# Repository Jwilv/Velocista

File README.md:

# Velocista, repocitorio de esquematicos, pcb y codigos de robots velocistas.

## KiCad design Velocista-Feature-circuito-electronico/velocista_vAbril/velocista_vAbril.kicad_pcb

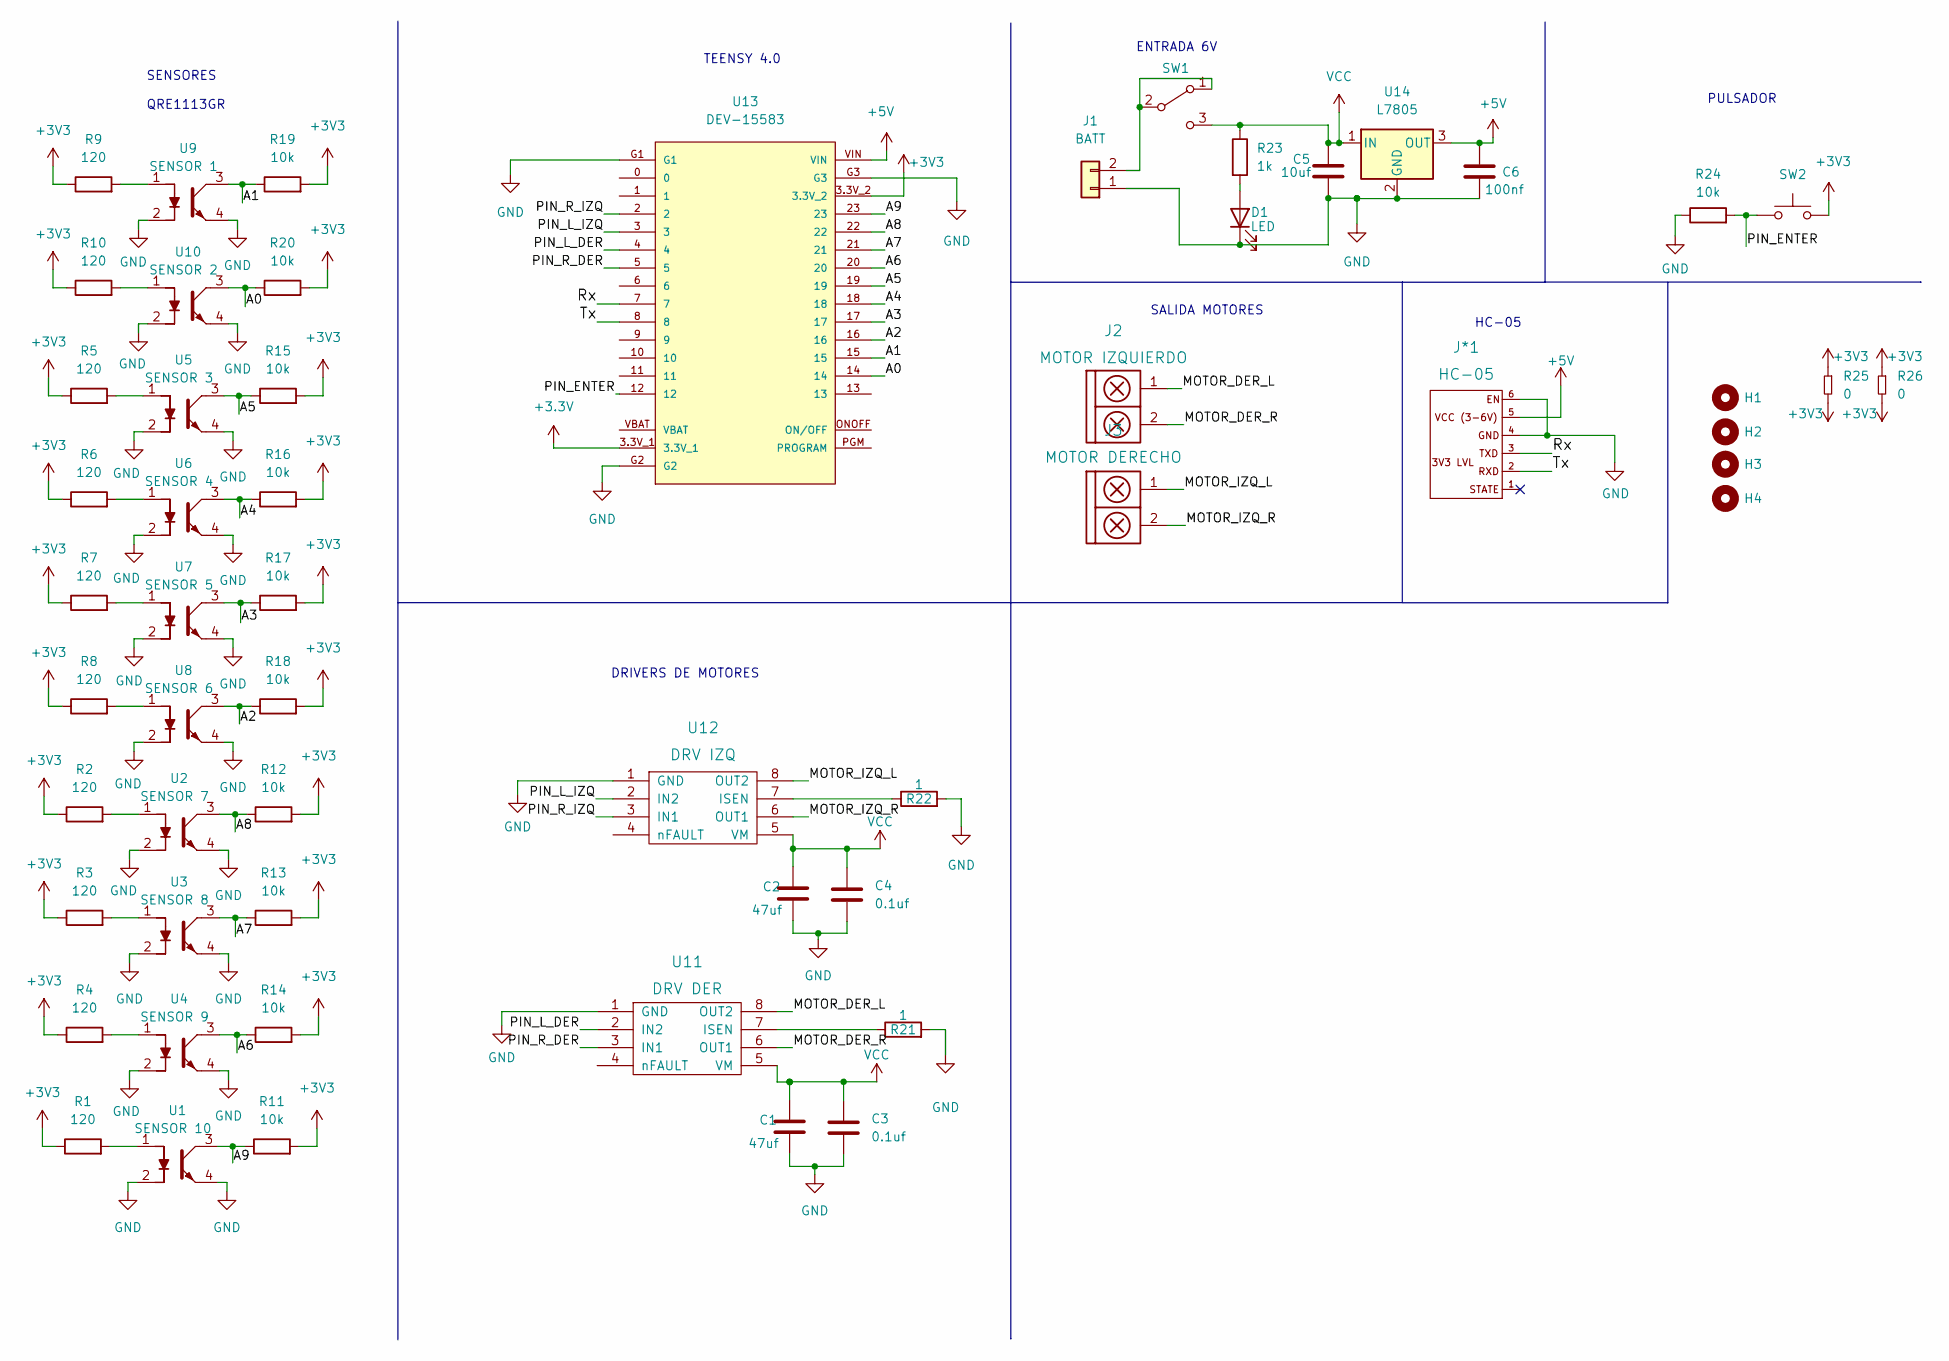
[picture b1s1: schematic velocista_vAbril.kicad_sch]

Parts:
C1, C2: 47uf; C_0805
C3, C4: 0.1uf; C_0805
C5: 10uf; C_0805
C6: 100nf; C_0805
D1: LED; led_3mm_clear
H1, H3: Mounting_Hole; hole_3mm
H2, H4: Mounting_Hole; Pololu_Micro_Con_Soporte_Simple
J1: BATT; JST_PH_B2B-PH-K_1x02_P2.00mm_Vertical
J2: MOTOR IZQUIERDO; JST_EH_B2B-EH-A_1x02_P2.50mm_Vertical
J3: MOTOR DERECHO; JST_EH_B2B-EH-A_1x02_P2.50mm_Vertical
J*1: HC-05
R1, R2, R3, R4, R5, R6, R7, R8, R9, R10: 120; R_0805
R11, R12, R13, R14, R15, R16, R17, R18, R19, R20, R24: 10k; R_0805
R21, R22: 1; R_0805
R23: 1k; R_0805
R25, R26: 0; RES0.3
SW1: SW_SPDT; SW_SPDT_TH_Vertical
SW2: SW_Push; Pulsador_TH_4
U1, U2, U3, U4, U5, U6, U7, U8, U9, U10: QRE1113; SOIC180P460X187-4N
U11: DRV DER; SSOP-8
U12: DRV IZQ; SSOP-8
U13: DEV-15583; MODULE_DEV-15583
U14: L7805; SOT223

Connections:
+5V: C6.1, J*1.5, U13.VIN, U14.3 (OUT)
/A0: R20.1, U10.3, U13.14
/A1: R19.1, U9.3, U13.15
/A2: R18.1, U8.3, U13.16
/A3: R17.1, U7.3, U13.17
/A4: R16.1, U6.3, U13.18
/A5: R15.1, U5.3, U13.19
/A6: R14.1, U4.3, U13.20
/A7: R13.1, U3.3, U13.21
/A8: R12.1, U2.3, U13.22
/A9: R11.1, U1.3, U13.23
/MOTOR_DER_L: J2.1, U11.8 (OUT2)
/MOTOR_DER_R: J2.2, U11.6 (OUT1)
/MOTOR_IZQ_L: J3.1, U12.8 (OUT2)
/MOTOR_IZQ_R: J3.2, U12.6 (OUT1)
/PIN_ENTER: R24.2, SW2.1, U13.12
/PIN_L_DER: U11.2 (IN2), U13.4
/PIN_L_IZQ: U12.2 (IN2), U13.3
/PIN_R_DER: U11.3 (IN1), U13.5
/PIN_R_IZQ: U12.3 (IN1), U13.2
/Rx: J*1.3, U13.7
/Tx: J*1.2, U13.8
GND: C1.2, C2.2, C3.2, C4.2, C5.2, C6.2, D1.1 (K), J1.1, J*1.4, J*1.6, R21.2, R22.2, R24.1, U1.2, U1.4, U2.2, U2.4, U3.2, U3.4, U4.2, U4.4, U5.2, U5.4, U6.2, U6.4, U7.2, U7.4, U8.2, U8.4, U9.2, U9.4, U10.2, U10.4, U11.1 (GND), U12.1 (GND), U13.G1, U13.G2, U13.G3, U14.2 (GND)
unnamed: D1.2 (A), R23.2
unnamed: J1.2, SW1.1 (A), SW1.2 (B)
unnamed: R1.2, U1.1
unnamed: R2.2, U2.1
unnamed: R3.2, U3.1
unnamed: R4.2, U4.1
unnamed: R5.2, U5.1
unnamed: R6.2, U6.1
unnamed: R7.2, U7.1
unnamed: R8.2, U8.1
unnamed: R9.2, U9.1
unnamed: R10.2, U10.1
unnamed: R21.1, U11.7 (ISEN)
unnamed: R22.1, U12.7 (ISEN)
VCC: C1.1, C2.1, C3.1, C4.1, C5.1, R23.1, SW1.3 (C), U11.5 (VM), U12.5 (VM), U14.1 (IN)

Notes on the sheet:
HC-05
DRIVERS DE MOTORES
ENTRADA 6V
SENSORES QRE1113GR
SALIDA MOTORES
TEENSY 4.0
PULSADOR

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
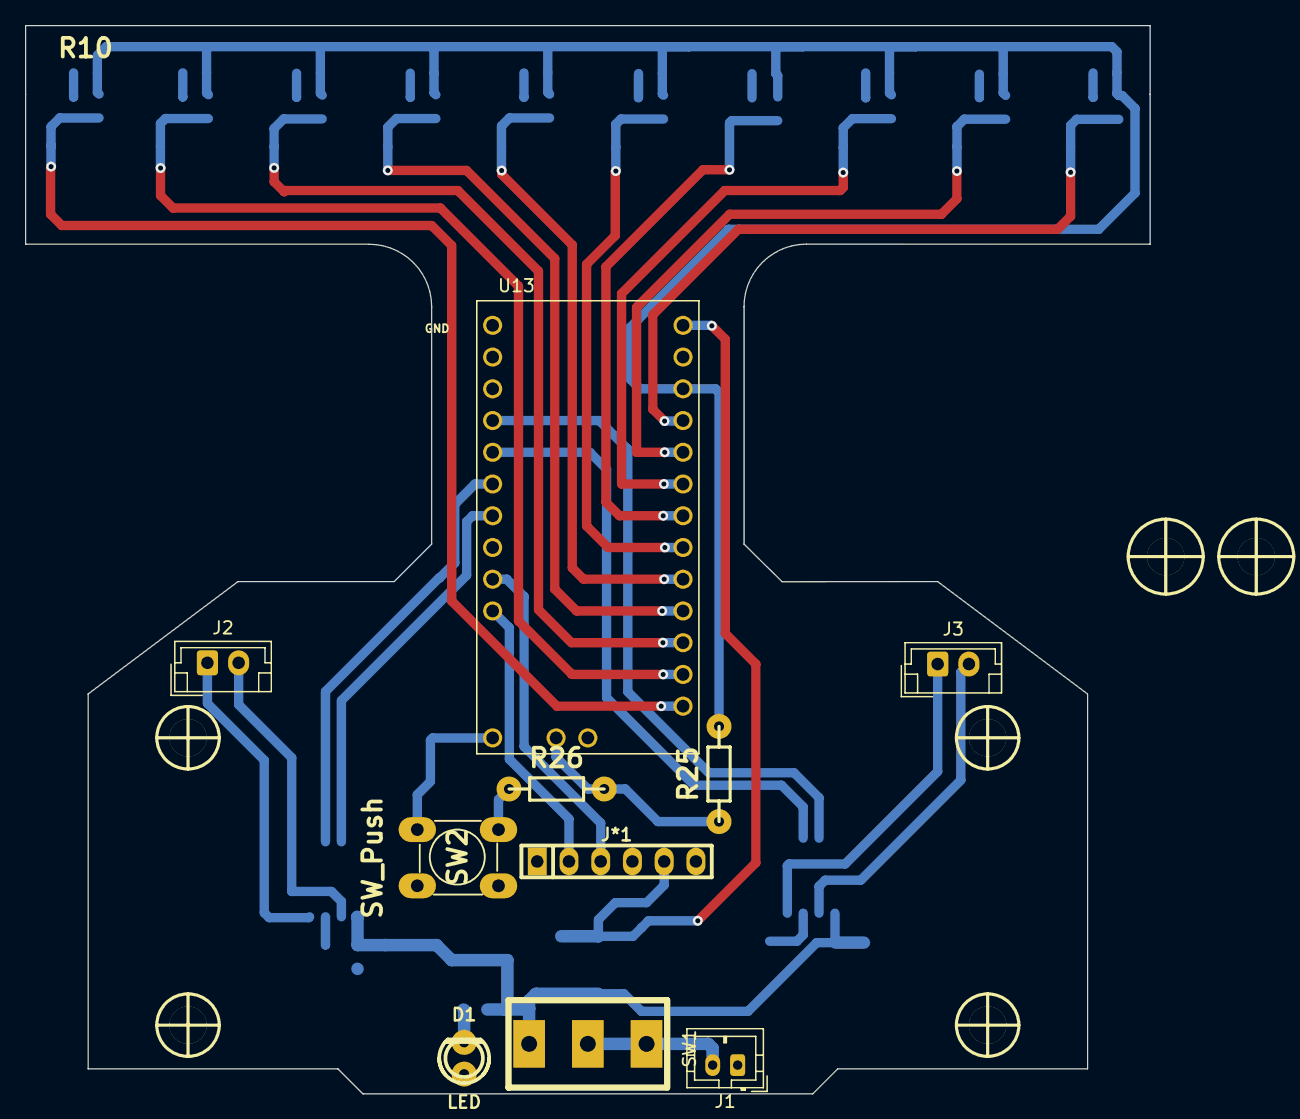
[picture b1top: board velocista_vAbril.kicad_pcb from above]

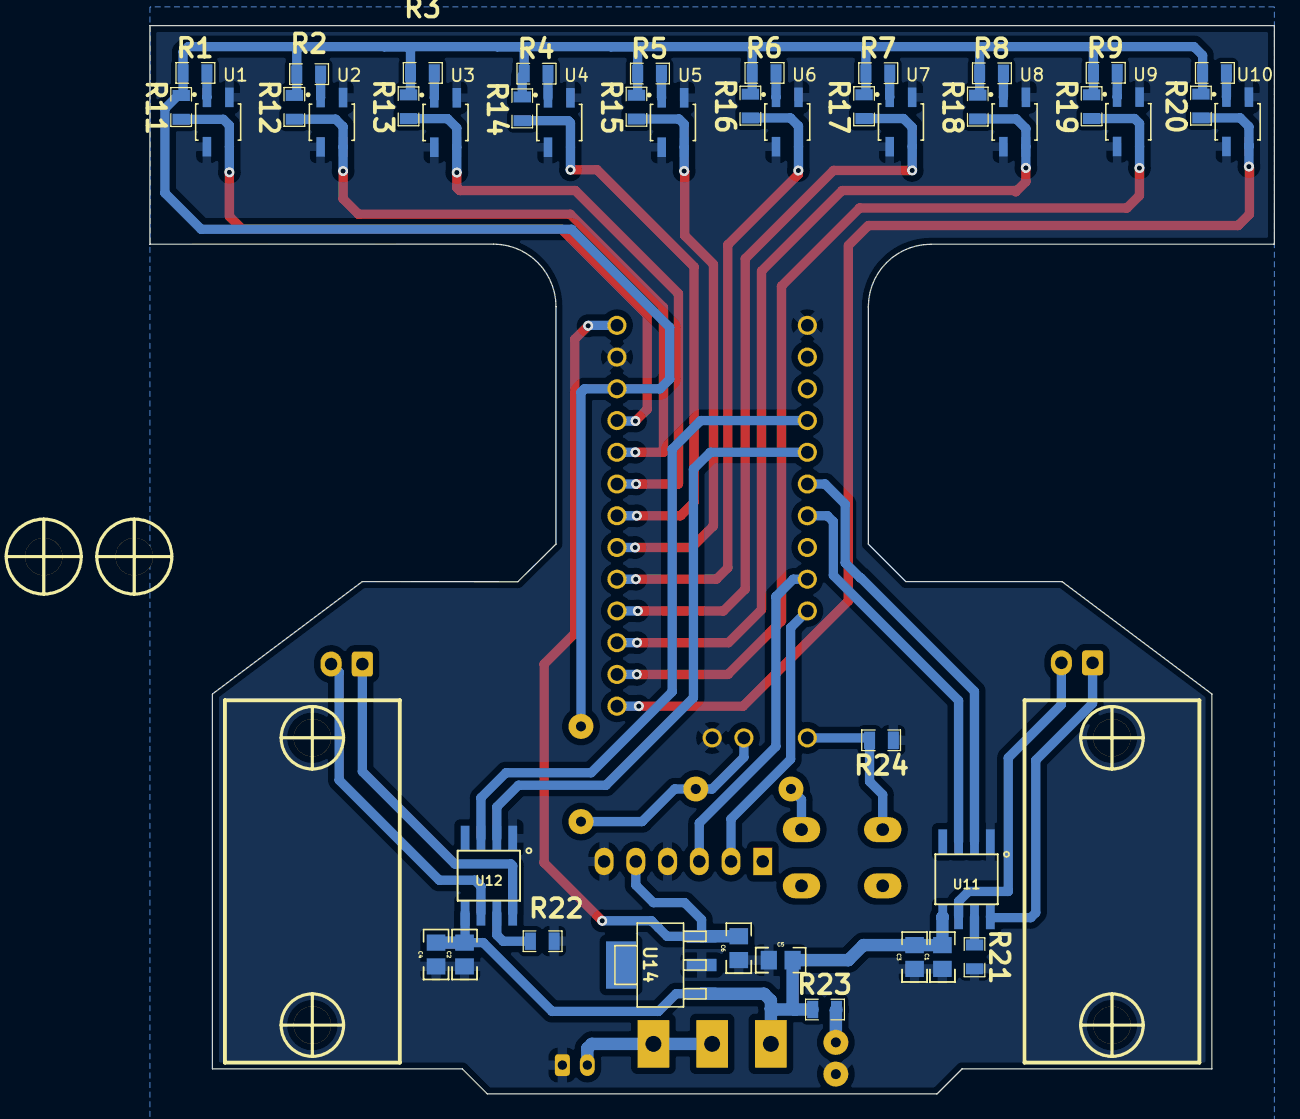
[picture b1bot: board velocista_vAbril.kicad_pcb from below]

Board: 2 copper layers, 90.0 x 85.5 mm, 57 parts (45 on the bottom side), 39 nets.

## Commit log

2022-10-03 code del velocista, con sensores incluidos
2022-10-04 detector de linea blanca con pines analogicos
2022-10-05 añadi posición
2022-10-08 falta sacar los test
2022-10-09 Create asdasd
2022-10-09 Rename tu romantico/asdasd to tu.romantico robot
2022-10-09 Create SDF SDF
2022-10-09 código tu romántico competencia utn
2022-10-10 placa velocista al 60%
    faltan enrutar los qre1113 y un par de cosas mas. Capaz se tenga que cambiar el modelo de chasis ._.
2022-10-19 agrege los valores de las sumas y defini los comandos
2022-10-19 paso por el debug
2022-10-31 pruebas para el lunes
2022-11-06 update optimización
2022-11-12 cambio de linea
    se cambio a seguidor de la linea blanca para la competencia del sábado
2022-11-12 código en beta para bolt
